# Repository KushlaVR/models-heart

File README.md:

# Model's Heart

## Breathe life into your model

Плата для керування електронікою моделі (статичної або рухомої)

Можливості:
* Керування через WIFI з телефона або ПК
* 5 незалежних каналів (світлодіоди/сервомотори)
* 1 Н-міст для підключення мотора (піковий струм до 3А)
* Вмонтована BMS 1S та контроллер заряду Li-Ion акумулятора з індикацією заряду
* Вмикання/вимикання 1 кнопкою (вже є на платі)
* Дистанційне вимкнення

# Поки ти читаєш цей текст - українці гинуть від російських ракет.
# While you are reading this text, Ukrainians are dying from russian missiles.

Ти можеш перерахувати будь-яку суму на спеціальний рахунок Національного Банку України для допомоги збройним силам україни у протистоянні російському окупанту.

Навіть незначна сума може врятувати чиєсь життя!

You can transfer any amount to a special account of the National Bank of Ukraine to help the armed forces of Ukraine in the fight against the Russian occupier.

Even a small amount can save someone's life!

### Для зарахування коштів у національній валюті:

```
Банк: Національний банк України
МФО 300001
Рахунок № UA843000010000000047330992708
код ЄДРПОУ 00032106
Отримувач: Національний банк України 
```
### To deposit funds in USD: 
```
BENEFICIARY: National Bank of Ukraine
BENEFICIARY BIC: NBUA UA UX
BENEFICIARY ADDRESS: 9 Instytutska St, Kyiv, 01601, Ukraine
ACCOUNT NUMBER: 804790258
BENEFICIARY BANK NAME: JP MORGAN CHASE BANK, New York
BENEFICIARY BANK BIC: CHASUS33
ABA 0210 0002 1
BENEFICIARY BANK ADDRESS: 383 Madison Avenue, New York, NY 10017, USA
PURPOSE OF PAYMENT: for ac 47330992708 
```
### To deposit funds in EUR: 
```
BENEFICIARY: National Bank of Ukraine
IBAN DE05504000005040040066
PURPOSE OF PAYMENT: for ac 47330992708
BENEFICIARY BANK NAME: DEUTSCHE  BUNDESBANK, Frankfurt
BENEFICIARY BANK BIC: MARKDEFF
BENEFICIARY BANK ADDRESS: Wilhelm-Epstein-Strasse 14, 60431 Frankfurt Am Main, Germany
```
### To deposit funds in GBP: 
```
BENEFICIARY/RECIPIENT NAME: National Bank of Ukraine
ACCOUNT NUMBER: 80033041
IBAN GB52CHAS60924280033041
BENEFICIARY ADDRESS: 9 Instytutska St, Kyiv, 01601, Ukraine
BENEFICIARY BANK NAME: JP MORGAN CHASE BANK NA, London
BENEFICIARY BANK BIC: CHASGB2L
SORT CODE: 60-92-42 
BENEFICIARY BANK ADDRESS: 125 London Wall, London EC2Y 5AJ, UK
PURPOSE OF PAYMENT: for ac 47330992708
```

## Як створювалась ця плата

https://www.youtube.com/watch?v=I-fucbyPBxc&list=PLNvbguf8aVrykSSVMaIyB5YiUsczeTyt5

Цей список відтворення містить детальний опис процесу проектування, виготовлення та створення прошивки для цього проекту з чистого листка.

# Schematic

# Board

# Що обрати Model's Heart чи Arduino?

Плата Model's Heart та Arduino  чи Wemos не є взаємозамінні. Вони схожі, проте мають і відмінності. Це як комп'ютери із різною комплектацією. 
Для коащого розуміння ознайомтесь із порівняльоню таблицею.

## Проівняльна таблиця Arduino Nano, Wemos D1, Model's Heart
| Характеристика |Arduino Nano | Wemos D1 | Model's Heart |
|---          |---|---|---|
| Процесор    |Atmega 328| ESP8266  | ESP8266 |
| Ядро        | 8-bit AVR RISC | Tensilica L106 32-bit RISC | Tensilica L106 32-bit RISC |
| Тип         | Microcontroller| Soc  | SoC |
|Оперативня пам'ять|2K bytes|50k bytes|50k bytes|
|Постійна пам'ять|32K bytes інтергрована| - | - |
|Зовнішня пам'ять| - | 16M bytes | 16M bytes |
|Частота процесора| 16MHz | 52MHz | 52Mhz |
|GPIO| 24 | 11 | 8 |
|Analog Pins| 8 | 1 | 1 |
|ADC| 1 | 1 | 1 |
|Точність ADC | 10bit | 10bit | 10bit |
|Wi-Fi | - | 2.4GHz | 2.4GHz |
|USB Power | micro USB | micro USB | Type-C |
|Живлення від Li-Ion | - | - | + |
|Li-Ion BMS | - | - | + |
|Li-Ion Charger | - | - | + |
|Power switch | - | - | + |
|H-Bridge | - | - | 3A (max) |

## У мене вже є плата Model's Heart, що далі?
Базовий набір:
* Завантажена з GitHub копія проекту
* Модуль, або відлагоджувальна плата Model's Heart, або інша  на базі процесора ESP8266 (Наприклад Wemos D1 mini, Lolin, і т.п.)
* Комп'ютер з USB
* Веб-переглядач для налаштування (наприклад Edge, Chrome, Mozilla, Safari, Opera ...)

Додаткові інструменти, якщо ви захочете переробити прошивку під більш складні задачі:
* Visual Studio Code
* Встановлена бібліотека Platformio

## Прошивка
У папці Tools є утиліта для прошивки та безпосередньо сам файл прошивки. Для більшості користувачів цього є цілком достатньо. Виконавши декілька простих кроків, ви зможете перетворити плату у радіоапаратуру для керування моделями.

Покрокова інструкція
1. Підключаєте плату до USB-порту вашого комп'ютера.
2. Встановлюєте драйвер CH340 (якщо його ще немає)
3. Заходите у диспетчер пристроїв і перевіряєте, чи всі драйвери встановлено і чи ваша плата розпізнається системою. 
  * Відкриваєте панель керування комп'ютером. 

  * Переходите на пункт "Диспетчер пристроїв".
Ймовірно, ваша плата буде називатися 'USB-Serial CH340 (COM_)'

  * Запам'ятовуєте, який номер порта отримала ваша плата (у моєму випадку - №3)

4. Запускаєте Tools/upload.bat
5. Після старту скрипт запитає номер порта, до якого під'єднано вашу плату
6. Вводите номер (тільки цифру), натискаєте Enter
7. Натискаєте кнопку Power на платі Model's Heart
8. Чекаєте, поки завершиться процес завантаження

Все - плата прошита.

З цього моменту нею можна користуватись.

## Встановлення поновлень
Поновлення відбувається аналогічно до прошивки. Завантажуєте нову версію репозиторію. А далі все по кроках...

Зважте на те, що прошивка повністю переписує все що є в пам'яті плати. Тобто, якщо ви завантажували в неї модифікації через файловий менеджер, то завантажте їх, щоб не втратити.

# Налаштування елементів UI
Усі елементи користувацького інтерфейсу використовують абсолютну координатну сітку.
Відлік координат починається у верхньому правому кутку.

Робоче поле має фіксовані пропорції 100:45

Розміри елементів інтерфейсу вказуються у відсотковому еквіваленті до ширини робочого поля.

Наприклад цей текстовий блок буде розміщений з відступом 10% з ліва, 20% з гори. Його ширина і висота відповідатимуть відповідно 30% ширини екрану та 40% ширини екрану. Зверніть увагу, що в обидвох випадках (ширина і висота блока) виміри прив'язані до % **ширини екрану**
```
    {
        "type":"text",
        "x": "10",
        "y": "20",
        "w": "30",
        "h": "40",
        "text":"текст"
    }
```

## Елементи графічного інтерфейсу
## Text

```
    {
        "type":"text",
        "x": int,
        "y": int,
        "w": int,
        "h": int,
        "text":string,
        "bg":string
    }
```

## Button
```
    {
        "type":"button",
        "x": int,
        "y": int,
        "w": int,
        "h": int,
        "text": string,
        "cmd": string
    }
```

## Slider
```
    {
        "type":"slider",
        "x": int,
        "y": int,
        "w": int,
        "h": int,
        "color": string,
        "cmd": string,
        "autocenter": bool,
    }
```

## Image
```
    {
        "type":"image",
        "x": int,
        "y": int,
        "w": int,
        "h": int,
        "cmd": string,
        "src": string,
        "autocenter": bool,
    }
```

## Toggle
```
    {
        "type":"toggle",
        "x": int,
        "y": int,
        "w": int,
        "h": int,
        "text": "Off|A|B|C",
        "values": "0|30|60|90",
        "cmd": string,
        "autocenter": bool,
    }
```

## Редактор графічного інтерфейсу
Плата обладнана редактором інтерфейсу. З допомого якого можна вносити зміни в існуючий дизайн, або створититповністю новий унікальний вигляд на ваш смак.

Для кожного елемента графічного інтерфейсу передбачено редактор властивостей.

## Графічний інтерфейс

## Сценарій

Сценарій визначає, як плата реагуватиме на команди користувача. У сценарію є лише одна властивість - "elements" (містить перелік команд)

```
{
    "elements" : [ {"cmd": string, ..}, {..}, ..]
}
```

Команди активуються у результаті взаємодії користувач з UI. Поки команда активна - її дії обробляються, інакше - ігноруються.

Структура команди:

- cmd - назва команди.
- type - тип команди
  * toggle - кожна активація команди вмикає/вимикає її стан
  * click - команда активна поки користувач утримує її значення відмінним від 0
  * none - команда не потребує активації. Вона активна завжди.
- actions - перелік дій, що будуть виконуватись поки команда активна.

```
{
    "cmd": string,
    "type": "toggle/click/none",
    "actions": 
        [
            {
                "type": 
                "cmd": string,
            },
            {
                "type": "motor",
                "speed": string (source of speed value for full H bridge). When set - a+b ignored
                "a": string (source of A half bridge values),
                "b": string (source of B half bridge values),
                "weight": int (in grams)
            },
            {
                "type": "blink",
                "points": [
                    {"pin": "1", "offset":"0", "value":"0"},
                    {"pin": "1", "offset":"500", "value":"255"},
                    {"pin": "1", "offset":"1000", "value":"0"}
                ]
            }
        ...
        ]
}
```
### Дії сценаріїв

#### Маячок
Дія перемикає виходи у заданій часовій точці.

- type - blink
- points - масив точок

Точка:
- pin - номер виходу
- offset - точка часу у мілісекундах. Відлік починається від старту дії
- value - PWM значення виходу

```
{
    "type": "blink",
    "points": [
        {"pin": "1", "offset":"0", "value":"0"},
        {"pin": "1", "offset":"500", "value":"255"},
        {"pin": "1", "offset":"1000", "value":"0"}
    ]
}
```

#### Мотор
Дія використовується для керування мотором.

- type - motor
- speed - назва команди яка використовуються для швидкості мотора
- weight - вага уявного маховика мотора. Використовується для імітації інерції

```
{
    "type":"motor",
    "speed":"motor_x",
    "weight": "80000"
}
```

## Приклади сценаріїв
### Керування гвинтовим літаком

ui.json
```
{
  "bg": "url('img/bg.jpg')",
  "elements": [
    {
      "type": "toggle",
      "x": 31,
      "y": 40.5,
      "w": 42,
      "h": 4,
      "text": "Max|Mid|Min|Off|Min|Mid|Max",
      "cmd": "motor_x",
      "values": "100|60|30|0|-30|-60|-100"
    },
    {
      "type": "slider",
      "x": 57.5,
      "y": 17.5,
      "w": 26.5,
      "h": 6,
      "cmd": "motor",
      "autocenter": "y"
    },
    {
      "type": "button",
      "x": 0,
      "y": 10,
      "w": 27,
      "h": 4,
      "text": "Хвостовий маячок",
      "cmd": "beacon"
    },
    {
      "type": "button",
      "x": 0,
      "y": 15,
      "w": 27,
      "h": 4,
      "text": "Габаритні маяки",
      "cmd": "strobe"
    },
    {
      "type": "button",
      "x": 0,
      "y": 20,
      "w": 27,
      "h": 4,
      "text": "Габарити",
      "cmd": "position"
    },
    {
      "type": "button",
      "x": 0,
      "y": 25,
      "w": 27,
      "h": 4,
      "text": "Посадкові вогні",
      "cmd": "navigation"
    },
    {
      "type": "button",
      "x": 0,
      "y": 30,
      "w": 27,
      "h": 4,
      "text": "Двигуни",
      "cmd": "ignition"
    },
    {
      "type": "text",
      "x": 31,
      "y": 37.5,
      "w": 18,
      "h": 3,
      "text": "Forward speed",
      "cmd": ""
    },
    {
      "type": "text",
      "x": 59.5,
      "y": 37.5,
      "w": 13.5,
      "h": 3,
      "text": "Reverse speed",
      "cmd": ""
    },
    {
      "text": "null",
      "cmd": "motor_x",
      "type": "image",
      "x": 46.5,
      "y": 14,
      "w": 10,
      "h": 10,
      "src": "img/green.png"
    },
    {
      "text": "null",
      "cmd": "motor_x",
      "type": "image",
      "x": 78.5,
      "y": 2,
      "w": 10,
      "h": 10,
      "src": "img/green.png"
    }
  ]
}
```

scripts.json
```
{
  "elements": [
    {
      "cmd": "beacon",
      "type": "toggle",
      "actions": [
        {
          "type": "blink",
          "points": [
            {
              "pin": "1",
              "offset": "0",
              "value": "0"
            },
            {
              "pin": "1",
              "offset": "0",
              "value": "0"
            },
            {
              "pin": "1",
              "offset": "100",
              "value": "20"
            },
            {
              "pin": "1",
              "offset": "200",
              "value": "50"
            },
            {
              "pin": "1",
              "offset": "300",
              "value": "90"
            },
            {
              "pin": "1",
              "offset": "400",
              "value": "50"
            },
            {
              "pin": "1",
              "offset": "500",
              "value": "20"
            },
            {
              "pin": "1",
              "offset": "600",
              "value": "0"
            },
            {
              "pin": "1",
              "offset": "1000",
              "value": "0"
            }
          ]
        }
      ]
    },
    {
      "cmd": "strobe",
      "type": "toggle",
      "actions": [
        {
          "type": "blink",
          "points": [
            {
              "pin": "4",
              "offset": "0",
              "value": "0"
            },
            {
              "pin": "4",
              "offset": "0",
              "value": "255"
            },
            {
              "pin": "4",
              "offset": "100",
              "value": "0"
            },
            {
              "pin": "4",
              "offset": "300",
              "value": "255"
            },
            {
              "pin": "4",
              "offset": "400",
              "value": "0"
            },
            {
              "pin": "4",
              "offset": "1000",
              "value": "0"
            }
          ]
        }
      ]
    },
    {
      "cmd": "position",
      "type": "toggle",
      "actions": [
        {
          "type": "blink",
          "points": [
            {
              "pin": "3",
              "offset": "0",
              "value": "0"
            },
            {
              "pin": "3",
              "offset": "0",
              "value": "255"
            },
            {
              "pin": "3",
              "offset": "1000",
              "value": "255"
            }
          ]
        }
      ]
    },
    {
      "cmd": "navigation",
      "type": "toggle",
      "actions": [
        {
          "type": "blink",
          "points": [
            {
              "pin": "2",
              "offset": "0",
              "value": "0"
            },
            {
              "pin": "2",
              "offset": "0",
              "value": "255"
            },
            {
              "pin": "2",
              "offset": "1000",
              "value": "255"
            }
          ]
        }
      ]
    },
    {
      "cmd": "ignition",
      "type": "toggle",
      "actions": [
        {
          "type":"motor",
          "speed":"motor_x",
          "weight": "80000"
        }
      ]
    }
  ]
}
```

# Підключення

## Чи можна розрізати плату?
Плата достатньо мініатюрна і необхідно постаратись її так прилаштувати, щоб не довелось її розрізати. Проте, якщо є необхідність "запакувати" по максимуму, то плату можна розрізати на 3 окремі частини. Після розрізання, їх можна об'єднати провідниками, або використовувати плату без них. Кожна із 3-ох частин є завершеним блоком.

## Підключення окремих блоків плати Model's Heart
### Плата зарядки
Плата зарядки - може використовуватись як зарядний пристрій Li-Ion акумуляторів.

### Плата програматора

Плату програматора можна використовувати як окремий USB<->TTL перетворювач.

### Основна плата
#### Підключення акумулятора

#### Підключення мотора

#### Підключення кнопки вкл./викл.

#### Підключення світлодіода до виходу #1

#### Підключення світлодіода до шини живлення #2
При підключенні світлодіода до шини живлення необхідно обмежити струм з допомогою резистора. Типовий струм для світлодіодів - 2мА

Опір обмежувального резистора можна розрахувати за законом Ома

```
Закон Ома

  I = U/R 

Де:
  I - струм, що протікає через коло в Амперах
  U - напруга на кінцях кола у Вольтах
  R - опір кола у Омах

Знаходимо R

  R = U/I 

  U = 4.2V
  I = 2mA = 0.002A

  R = 4.2V / 0.002A 
  R = 2100 Ом => 2.1KOм

```

# Web API

Взаємодія web інтерфейсу та плати відбувається по WIF з допомогою HTTP запитів.

Плата Model's Heart дозволяє одночасне керування з кількох клієнтів.
Для того, щоб надіслані команди відпрацьовувались платою - необхідна авторизація (GET api/EventSourceName). У відповідь ми отримаємо endpoint з допомогою якого можна підписатись на HTTP Events (GET /api/events), щоб отримувати інформацію від плати. Також, щоразу як користувач змінив стан поля відбувається пересилка цього стану у плату (POST api/post)

## GET api/EventSourceName
Метод повертає Endpoint (адресу джерела Events) по якому транслюється інформація з плати на web-UI. Одним із параметрів є ID клієнта

## GET /api/events 
Встановлюється як EventSource для сторінки Web інтерфейсу
Детальніше тут ->  https://developer.mozilla.org/en-US/docs/Web/API/EventSource

## POST api/post
Надсилаємо інформацію про поле на плату
```
{
  client:"random string id of client"
  format:[field1, field2, field, ... fieldN],
  values:['v1', 'v2', 'v3', .. 'vN']
}
```

- client - ID клієнта
- format - назви полів які наявні у інтерфейсі. Надсилається лише один раз. Всі інші рази ігнорується. Цього формату має притримуватись додаток при комунікації з приладом, і в такому ж форматі має відповідати плата. (це для того, щоб мінімізувати трафік і одночасно забезпечити підтримку стрих версій додатку у яких може бути інша конфігурація елементів керування)
- values - значення полів у посортовані відповідно до format.

## Алгоритм взаємодії
1. Авторизація
2. Налаштовуємо EventSource. 
3. POST api/post формат даних
4. По Event source каналу отримуємо від плати масив значень і розставляємо їх по елементах керування у відповідності до обговореного формату
5. Якщо користувач змінив якийсь параметр - надсилаємо платі пакет у обговореному наперед форматі. (Повертаємось до п4)
6. Якщо зв'язок втрачено - запускаємо зворотній відлік на 3 секунди і пробуємо відновити зв'язок (Повертаємось до п1)

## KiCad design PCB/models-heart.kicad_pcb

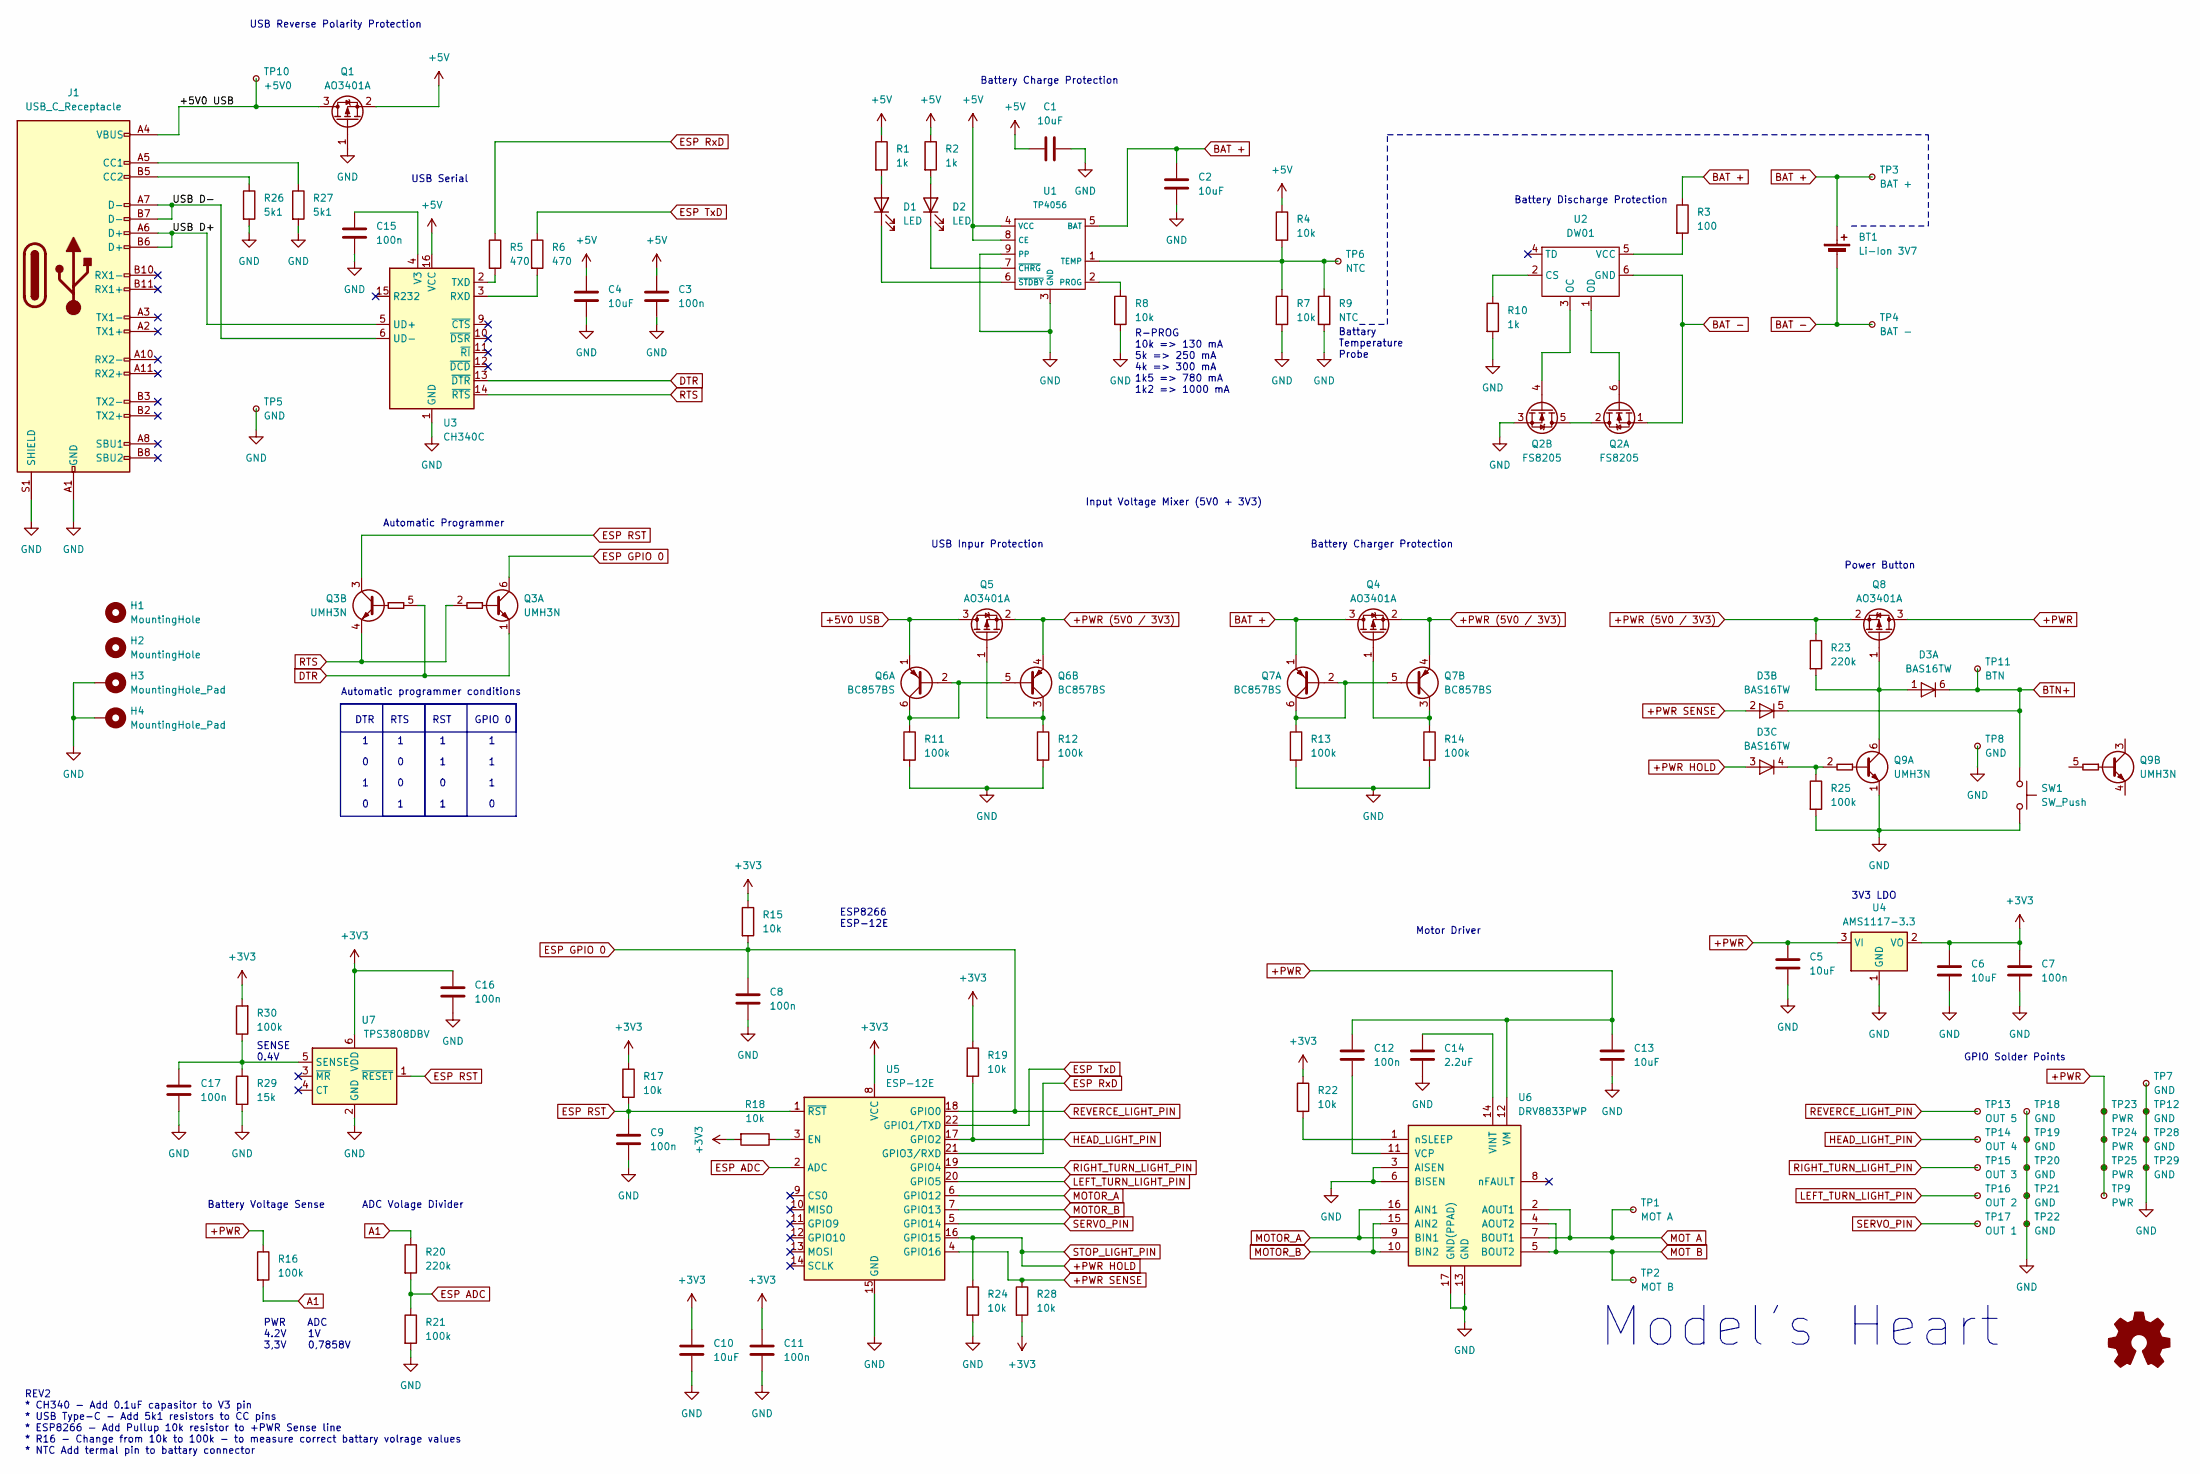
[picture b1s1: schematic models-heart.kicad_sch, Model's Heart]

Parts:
BT1: Li-Ion 3V7
C1, C2, C4, C5, C6, C10, C13: 10uF; C_1206_3216Metric; LCSC C13585
C3, C7, C8, C9, C11, C12, C15, C16, C17: 100n; C_0402_1005Metric; LCSC C307331
C14: 2.2uF; C_0805_2012Metric; LCSC C49217
D1: LED; LED_0603_1608Metric; LCSC C2286
D2: LED; LED_0603_1608Metric; LCSC C2290
D3: BAS16TW; SOT-363_SC-70-6; LCSC C68955
H1, H2: MountingHole; MountingHole_2.2mm_M2
H3, H4: MountingHole_Pad; MountingHole_2.2mm_M2_Pad_Via
J1: USB_C_Receptacle; USB_C_Receptacle_GCT_USB4115-03-C; LCSC C3039318
Q1, Q4, Q5, Q8: AO3401A; SOT-23; LCSC C15127
Q2: FS8205; SOT-23-6; LCSC C908265
Q3, Q9: UMH3N; SOT-363_SC-70-6; LCSC C62892
Q6, Q7: BC857BS; SOT-363_SC-70-6; LCSC C699266
R1, R2, R10: 1k; R_0402_1005Metric; LCSC C21190
R3: 100; R_0402_1005Metric; LCSC C22775
R4, R7, R8, R15, R17, R18, R19, R22, R24, R28: 10k; R_0402_1005Metric; LCSC C25804
R5, R6: 470; R_0402_1005Metric; LCSC C23179
R9: NTC; R_0603_1608Metric
R11, R12, R13, R14, R16, R21, R25, R30: 100k; R_0402_1005Metric; LCSC C25803
R20, R23: 220k; R_0402_1005Metric; LCSC C22961
R26, R27: 5k1; R_0402_1005Metric; LCSC C23186
R29: 15k; R_0402_1005Metric; LCSC C25804
SW1: SW_Push; SW_Push_SPST_NO_Alps_SKRK; LCSC C2905174
TP1: MOT A; TestPoint_Pad_D1.0mm
TP2: MOT B; TestPoint_Pad_D1.0mm
TP3: BAT +; TestPoint_Pad_D1.0mm
TP4: BAT -; TestPoint_Pad_D1.0mm
TP5, TP7, TP8, TP12, TP18, TP19, TP20, TP21, TP22, TP28, TP29: GND; TestPoint_Pad_D1.0mm
TP6: NTC; TestPoint_Pad_D1.0mm
TP9, TP23, TP24, TP25: PWR; TestPoint_Pad_D1.0mm
TP10: +5V0; TestPoint_Pad_D1.0mm
TP11: BTN; TestPoint_Pad_D1.0mm
TP13: OUT 5; TestPoint_Pad_D1.0mm
TP14: OUT 4; TestPoint_Pad_D1.0mm
TP15: OUT 3; TestPoint_Pad_D1.0mm
TP16: OUT 2; TestPoint_Pad_D1.0mm
TP17: OUT 1; TestPoint_Pad_D1.0mm
U1: TP4056; SOIC-8-1EP_3.9x4.9mm_P1.27mm_EP2.29x3mm; LCSC C16581
U2: DW01; SOT-23-6; LCSC C917079
U3: CH340C; SOIC-16_3.9x9.9mm_P1.27mm; LCSC C84681
U4: AMS1117-3.3; SOT-89-3; LCSC C880752
U5: ESP-12E; LCSC C89297
U6: DRV8833PWP; HTSSOP-16-1EP_4.4x5mm_P0.65mm_EP3.4x5mm_Mask2.46x2.31mm_The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; LCSC C50506
U7: TPS3808DBV; SOT-23-6; LCSC C19653

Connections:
+3V3: C6.1, C7.1, C10.1, C11.1, C16.1, R15.1, R17.1, R18.2, R19.1, R22.1, R28.2, R30.2, U4.2 (VO), U5.8 (VCC), U7.6 (VDD)
+5V: C1.1, C3.1, C4.1, Q1.2 (S), R1.1, R2.1, R4.1, U1.4 (VCC), U1.8 (CE), U3.16 (VCC)
+5V0 USB: J1.A4 (VBUS), J1.A9 (VBUS), J1.B4 (VBUS), J1.B9 (VBUS), Q1.3 (D), Q5.3 (D), Q6.1 (E1), TP10.1
+PWR: C5.1, C12.1, C13.1, Q8.3 (D), R16.1, TP9.1, TP23.1, TP24.1, TP25.1, U4.3 (VI), U6.12 (VM)
+PWR (5V0 / 3V3): Q4.2 (S), Q5.2 (S), Q6.4 (E2), Q7.4 (E2), Q8.2 (S), R23.1
+PWR HOLD: D3.3 (A), R24.1, U5.16 (GPIO15)
+PWR SENSE: D3.2 (A), R28.1, U5.4 (GPIO16)
/USB D+: J1.A6 (D+), J1.B6 (D+), U3.5 (UD+)
/USB D-: J1.A7 (D-), J1.B7 (D-), U3.6 (UD-)
A1: R16.2, R20.1
BAT +: BT1.1 (+), C2.2, Q4.3 (D), Q7.1 (E1), R3.1, TP3.1, U1.5 (BAT)
BAT -: BT1.2 (-), Q2.1 (S), TP4.1, U2.6 (GND)
BTN+: D3.5 (K), D3.6 (K), SW1.1, TP11.1
DTR: Q3.1 (E1), Q3.5 (B2), U3.13 (~DTR)
ESP ADC: R20.2, R21.1, U5.2 (ADC)
ESP GPIO 0: C8.1, Q3.6 (C1), R15.2, TP13.1, U5.18 (GPIO0)
ESP RST: C9.1, Q3.3 (C2), R17.2, U5.1 (~RST), U7.1 (~RESET)
ESP RxD: R5.1, U5.21 (GPIO3/RXD)
ESP TxD: R6.1, U5.22 (GPIO1/TXD)
GND: C1.2, C2.1, C3.2, C4.2, C5.2, C6.2, C7.2, C8.2, C9.2, C10.2, C11.2, C13.2, C14.2, C15.2, C16.2, C17.2, H3.1, H4.1, J1.A1 (GND), J1.A12 (GND), J1.B1 (GND), J1.B12 (GND), J1.S1 (SHIELD), Q1.1 (G), Q2.3 (S), Q9.1 (E1), R7.2, R8.2, R9.2, R10.2, R11.2, R12.2, R13.2, R14.2, R21.2, R24.2, R25.2, R26.2, R27.2, R29.2, SW1.2, TP5.1, TP7.1, TP8.1, TP12.1, TP18.1, TP19.1, TP20.1, TP21.1, TP22.1, TP28.1, TP29.1, U1.3 (GND), U1.9 (PP), U3.1 (GND), U4.1 (GND), U5.15 (GND), U6.3 (AISEN), U6.6 (BISEN), U6.13 (GND), U6.17 (GND(PPAD)), U7.2 (GND)
HEAD_LIGHT_PIN: R19.2, TP14.1, U5.17 (GPIO2)
LEFT_TURN_LIGHT_PIN: TP16.1, U5.20 (GPIO5)
MOT A: TP1.1, U6.2 (AOUT1), U6.7 (BOUT1)
MOT B: TP2.1, U6.4 (AOUT2), U6.5 (BOUT2)
MOTOR_A: U5.6 (GPIO12), U6.9 (BIN1), U6.16 (AIN1)
MOTOR_B: U5.7 (GPIO13), U6.10 (BIN2), U6.15 (AIN2)
unnamed: D1.2 (A), R1.2
unnamed: D1.1 (K), U1.6 (~STDBY)
unnamed: D2.2 (A), R2.2
unnamed: D2.1 (K), U1.7 (~CHRG)
unnamed: D3.1 (A), Q8.1 (G), Q9.6 (C1), R23.2
unnamed: D3.4 (K), Q9.2 (B1), R25.1
unnamed: J1.A5 (CC1), R27.1
unnamed: J1.B5 (CC2), R26.1
unnamed: Q2.2 (D), Q2.5 (D)
unnamed: Q2.6 (G), U2.1 (OD)
unnamed: Q2.4 (G), U2.3 (OC)
unnamed: Q4.1 (G), Q7.3 (C2), R14.1
unnamed: Q5.1 (G), Q6.3 (C2), R12.1
unnamed: Q6.2 (B1), Q6.5 (B2), Q6.6 (C1), R11.1
unnamed: Q7.2 (B1), Q7.5 (B2), Q7.6 (C1), R13.1
unnamed: R8.1, U1.2 (PROG)
unnamed: R4.2, R7.1, R9.1, TP6.1, U1.1 (TEMP)
unnamed: R10.1, U2.2 (CS)
unnamed: R3.2, U2.5 (VCC)
unnamed: R6.2, U3.3 (RXD)
unnamed: R5.2, U3.2 (TXD)
unnamed: C15.1, U3.4 (V3)
unnamed: R18.1, U5.3 (EN)
unnamed: C12.2, U6.11 (VCP)
unnamed: C14.1, U6.14 (VINT)
unnamed: R22.2, U6.1 (nSLEEP)
unnamed: C17.1, R29.1, R30.1, U7.5 (SENSE)
RIGHT_TURN_LIGHT_PIN: TP15.1, U5.19 (GPIO4)
RTS: Q3.2 (B1), Q3.4 (E2), U3.14 (~RTS)
SERVO_PIN: TP17.1, U5.5 (GPIO14)

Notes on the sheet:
Input Voltage Mixer (5V0 + 3V3)
Model's Heart
USB Reverse Polarity Protection
Battary Temperature Probe
RTS
DTR
ESP8266 ESP-12E
RST
Battery Charger Protection
ADC Volage Divider
REV2 * CH340 - Add 0.1uF capasitor to V3 pin * USB Type-C - Add 5k1 resistors to CC pins * ESP8266 - Add Pullup 10k resistor to +PWR Sense line * R16 - Change from 10k to 100k - to measure correct battary volrage values * NTC Add termal pin to battary connector
USB Inpur Protection
GPIO Solder Points
R-PROG 10k => 130 mA 5k => 250 mA 4k => 300 mA 1k5 => 780 mA 1k2 => 1000 mA
Automatic Programmer
Motor Driver
Battery Charge Protection
Automatic programmer conditions
PWR ADC 4.2V 1V 3,3V 0,7858V
USB Serial
Power Button
Battery Voltage Sense
SENSE 0.4V
GPIO 0
Battery Discharge Protection
3V3 LDO

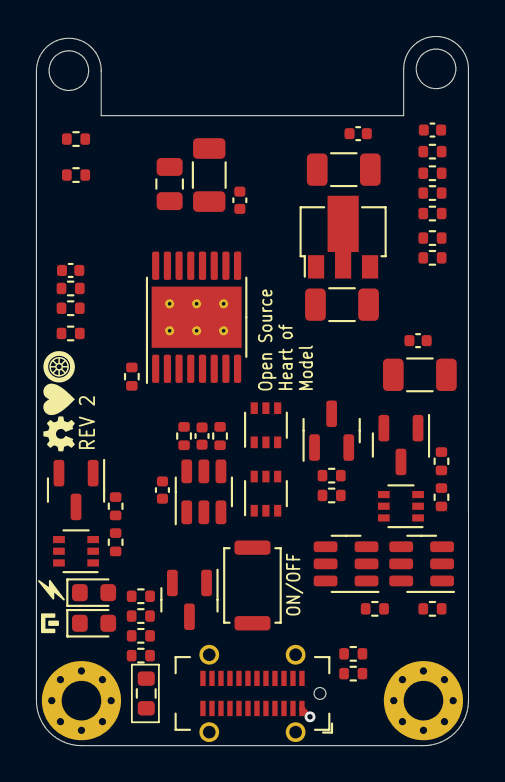
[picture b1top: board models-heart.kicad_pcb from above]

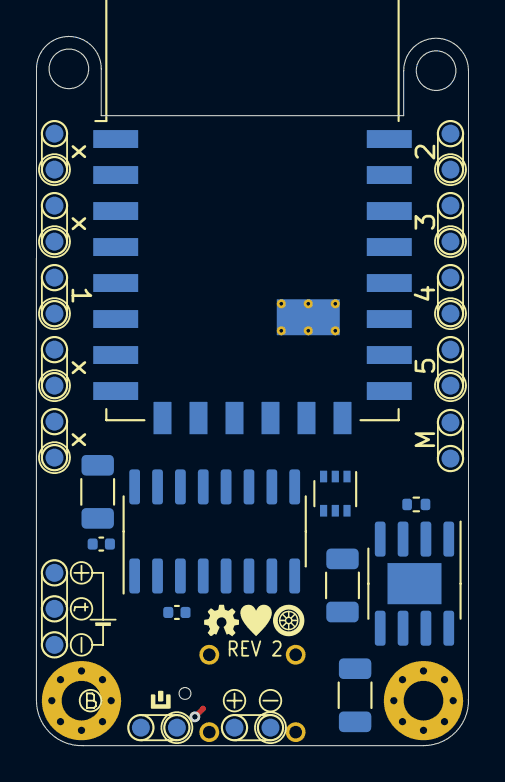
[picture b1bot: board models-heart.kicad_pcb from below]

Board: 4 copper layers, 24.0 x 39.4 mm, 99 parts (37 on the bottom side), 56 nets.

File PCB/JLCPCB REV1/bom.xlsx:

Comment | Designator | Footprint | JLCPCB Part # | Quantity
FS8205 | Q2 | Package_TO_SOT_SMD:SOT-23-6 | C908265 | 1
UMH3N | Q3, Q9 | Package_TO_SOT_SMD:SOT-363_SC-70-6 | C62892 | 2
BC857BS | Q6, Q7 | Package_TO_SOT_SMD:SOT-363_SC-70-6 | C699266 | 2
1k | R1, R2, R10 | Resistor_SMD:R_0603_1608Metric | C21190 | 3
100 | R3 | Resistor_SMD:R_0603_1608Metric | C22775 | 1
10k | R4, R7, R8, R15, R16, R17, R18, R19, R22, R24 | Resistor_SMD:R_0603_1608Metric | C25804 | 10
470 | R5, R6 | Resistor_SMD:R_0603_1608Metric | C23179 | 2
100k | R11, R12, R13, R14, R21, R25 | Resistor_SMD:R_0603_1608Metric | C25803 | 6
220k | R20, R23 | Resistor_SMD:R_0603_1608Metric | C22961 | 2
10uF | C1, C2, C4, C5, C6, C10, C13 | Capacitor_SMD:C_1206_3216Metric | C13585 | 7
SW_Push | SW1 | Button_Switch_SMD:SW_SPST_EVQP7C | C115362 | 1
0.1uF | C3, C7, C8, C9, C11, C12 | Capacitor_SMD:C_0603_1608Metric | C913910 | 6
2.2uF | C14 | Capacitor_SMD:C_0805_2012Metric | C49217 | 1
TP4056 | U1 | Package_SO:SOIC-8-1EP_3.9x4.9mm_P1.27mm_EP2.29x3mm | C16581 | 1
DW01 | U2 | Package_TO_SOT_SMD:SOT-23-6 | C917079 | 1
CH340C | U3 | Package_SO:SOIC-16_3.9x9.9mm_P1.27mm | C84681 | 1
AMS1117-3.3 | U4 | Package_TO_SOT_SMD:SOT-89-3 | C880752 | 1
ESP-12E | U5 | RF_Module:ESP-12E | C89297 | 1
DRV8833PWP | U6 | Package_SO:HTSSOP-16-1EP_4.4x5mm_P0.65mm_EP3.4x5mm_Mask2.46x2.31mm_ThermalVias | C50506 | 1
LED | D1 | LED_SMD:LED_0603_1608Metric | C2286 | 1
LED | D2 | LED_SMD:LED_0603_1608Metric | C2290 | 1
BAS16TW | D3 | Package_TO_SOT_SMD:SOT-363_SC-70-6 | C68955 | 1
USB_C_Plug | P1 | Connector_USB:USB_C_Receptacle_GCT_USB4105-xx-A_16P_TopMnt_Horizontal | C2927038 | 1
AO3401A | Q1, Q4, Q5, Q8 | Package_TO_SOT_SMD:SOT-23 | C15127 | 4

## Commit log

2023-07-20 Layout REV1
2023-07-22 Layout
2023-07-22 Schematic
2023-07-22 minor fixes
2023-07-22 readme
2023-07-22 Release candidate
2023-07-24 Trace Almost Done
2023-07-26 PCB Done
2023-07-29 Production
2023-07-29 Update image files
2023-07-29 remove backup cdr
2023-07-29 Cleanup folders
2023-07-29 update board render
2023-08-01 Fabrication
2023-08-12 Production Complete
2023-08-18 Part 5
2023-08-27 Part 6
2023-08-29 HardwareTest
2023-08-29 Rev 1
2023-08-29 Тестові налаштування
2023-08-29 git ignore
2023-08-29 Concept proof
2023-08-31 Parser works
2023-08-31 ui fix
2023-08-31 Refactor UI folder
2023-08-31 type fix
2023-09-03 UI in progress
2023-09-03 ui prototype
2023-09-03 ui.json update
2023-09-04 ui generator works
2023-09-08 SCript engine ready
2023-09-09 зфке 8
2023-09-16 Part 9
2023-09-18 dev-server
2023-09-23 UI test
2023-09-26 Part 11
2023-10-04 actionns test
2023-10-04 Actions
2023-10-04 release test
2023-10-04 tag test
2023-10-04 rev1
2023-10-04 test
2023-10-10 REV1 - File manager
2023-10-10 tools
2023-10-10 littlefs.bin
2023-10-12 куфвьу
2023-10-12 docs
2023-10-16 typo
2023-10-16 designer
2023-10-17 Designer-basics
2023-10-21 part 14
2023-10-22 part 15
2023-10-23 Bug fixes
2023-10-24 Beat 1
2023-10-25 Add Toggle button
2023-10-25 Save state
2023-10-25 firmware
2023-10-25 GUI Editor
2023-11-05 Image selector
2023-11-07 auto actions
2023-11-09 Add index-custom.html
2023-11-19 Checkbox + File upload + Save state + other
2023-11-22 startup speed
2023-11-25 power cutoff
2023-12-10 Release
2023-12-17 REV2
2023-12-18 placement
